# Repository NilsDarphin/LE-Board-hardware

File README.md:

#LE-Board-hardware

## The LEB Project

LEB is a college project which purpose is to allow you to control remotely the I/Os of a microcontroller.
The project consists of a Bluetooth low energy shield, its firmware, and an Android application.

**LEB works with the following projects :**

Repository  | Description
------------- | -------------
NilsDarphin/LEBoard_hardware      |Schematics and design of the board (Eagle files)
NilsDarphin/LEBoard_firmware      |Firmware of the board
NilsDarphin/LEB_Android           |Example of Android application

### Exemples of use

[Control the IOs from your Android](http://www.youtube.com/watch?v=B23XFl-bA60)

[Control a Car/Robot from your Android](http://www.youtube.com/watch?v=EagJ7pZ6EUM)

### What is it used for ?

The LEB Project allows you to develop easily Bluetooth low energy peripherals : 
Plug a LEB shield on your circuit and develop your own IOS or Android application.
You don't need to program the shield, everything is managed by the client (Smartphone, computer or smart home box...), so you have little electronic to do and no C/C++.

## The LEB Hardware

This repository contains the shield and the design of the LEB shield. You will need Eagle 6.0+ to open the files.

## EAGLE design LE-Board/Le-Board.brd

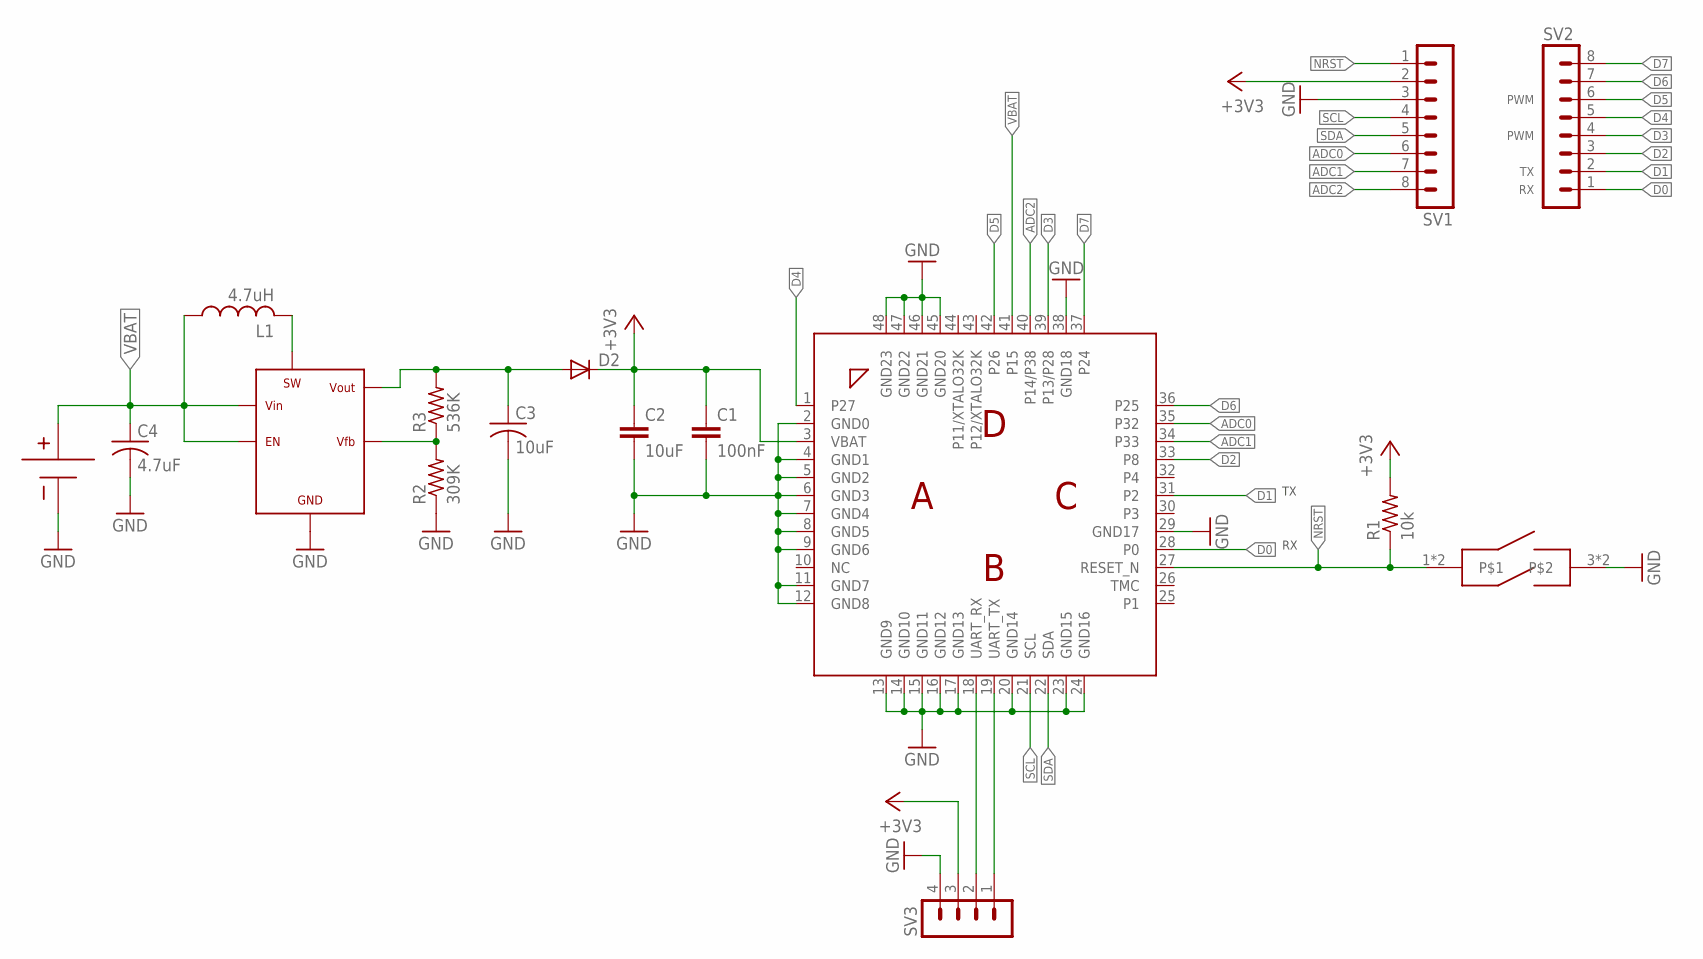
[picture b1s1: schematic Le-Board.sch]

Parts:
C1: 100nF; C0603
C2, C3: 10uF; C0603
C4: 4.7uF; C0603
D2: DIODE-DO214AA; DO214AA
L1: 4.7uH; L2825P
R1: 10k; R0603
R2: 309K; R0603
R3: 536K; R0603
SV1, SV2: MA08-1
SV3: MA04-1
U$1: BCM20732S; LGA-48
U$5: ELEVATOR
U$10: FSM4JSMA
U$17: CR2032_HLD; CR2031_BAT_HLD

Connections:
+3V3: C1.1, C2.1, D2.C, R1.2, SV1.2, SV3.3, U$1.3 (VBAT)
ADC0: SV1.6, U$1.35 (P32)
ADC1: SV1.7, U$1.34 (P33)
ADC2: SV1.8, U$1.40 (P14/P38)
D0: SV2.1, U$1.28 (P0)
D1: SV2.2, U$1.31 (P2)
D2: SV2.3, U$1.33 (P8)
D3: SV2.4, U$1.39 (P13/P28)
D4: SV2.5, U$1.1 (P27)
D5: SV2.6, U$1.42 (P26)
D6: SV2.7, U$1.36 (P25)
D7: SV2.8, U$1.37 (P24)
GND: C1.2, C2.2, C3.2, C4.2, R2.1, SV1.3, SV3.4, U$1.2 (GND0), U$1.4 (GND1), U$1.5 (GND2), U$1.6 (GND3), U$1.7 (GND4), U$1.8 (GND5), U$1.9 (GND6), U$1.11 (GND7), U$1.12 (GND8), U$1.13 (GND9), U$1.14 (GND10), U$1.15 (GND11), U$1.16 (GND12), U$1.17 (GND13), U$1.20 (GND14), U$1.23 (GND15), U$1.24 (GND16), U$1.29 (GND17), U$1.38 (GND18), U$1.45 (GND20), U$1.46 (GND21), U$1.47 (GND22), U$1.48 (GND23), U$5.2 (GND), U$10.3, U$10.4, U$17.BOT (-)
HCI_RX: SV3.2, U$1.18 (UART_RX)
HCI_TX: SV3.1, U$1.19 (UART_TX)
unnamed: C3.1, D2.A, R3.2, U$5.5 (VOUT)
unnamed: R2.2, R3.1, U$5.4 (VFB)
unnamed: L1.2, U$5.1 (SW)
NRST: R1.1, SV1.1, U$1.27 (RESET_N), U$10.1, U$10.2
SCL: SV1.4, U$1.21 (SCL)
SDA: SV1.5, U$1.22 (SDA)
VBAT: C4.1, L1.1, U$1.41 (P15), U$5.3 (EN), U$5.6 (VIN), U$17.TOP1 (+), U$17.TOP2 (+)

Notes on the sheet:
PWM

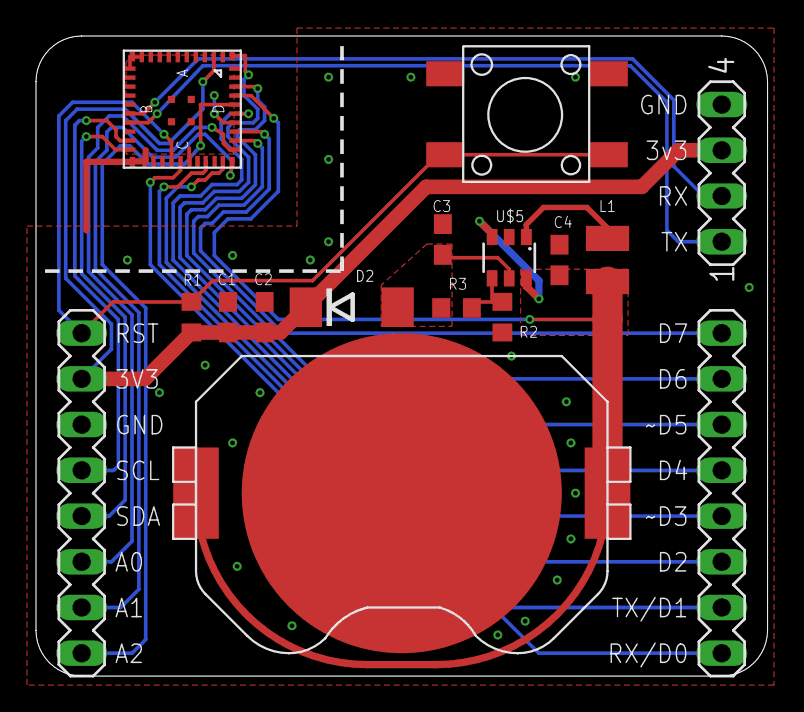
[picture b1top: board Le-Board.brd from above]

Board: 2 copper layers, 40.6 x 35.6 mm, 16 parts (0 on the bottom side), 22 nets.

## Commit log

2014-12-15 LE Board v1.0
2014-12-15 Added BOM
